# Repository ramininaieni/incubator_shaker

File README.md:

# incubator_shaker
Firmware for an open source incubator shaker to make genetic engineering more accessible

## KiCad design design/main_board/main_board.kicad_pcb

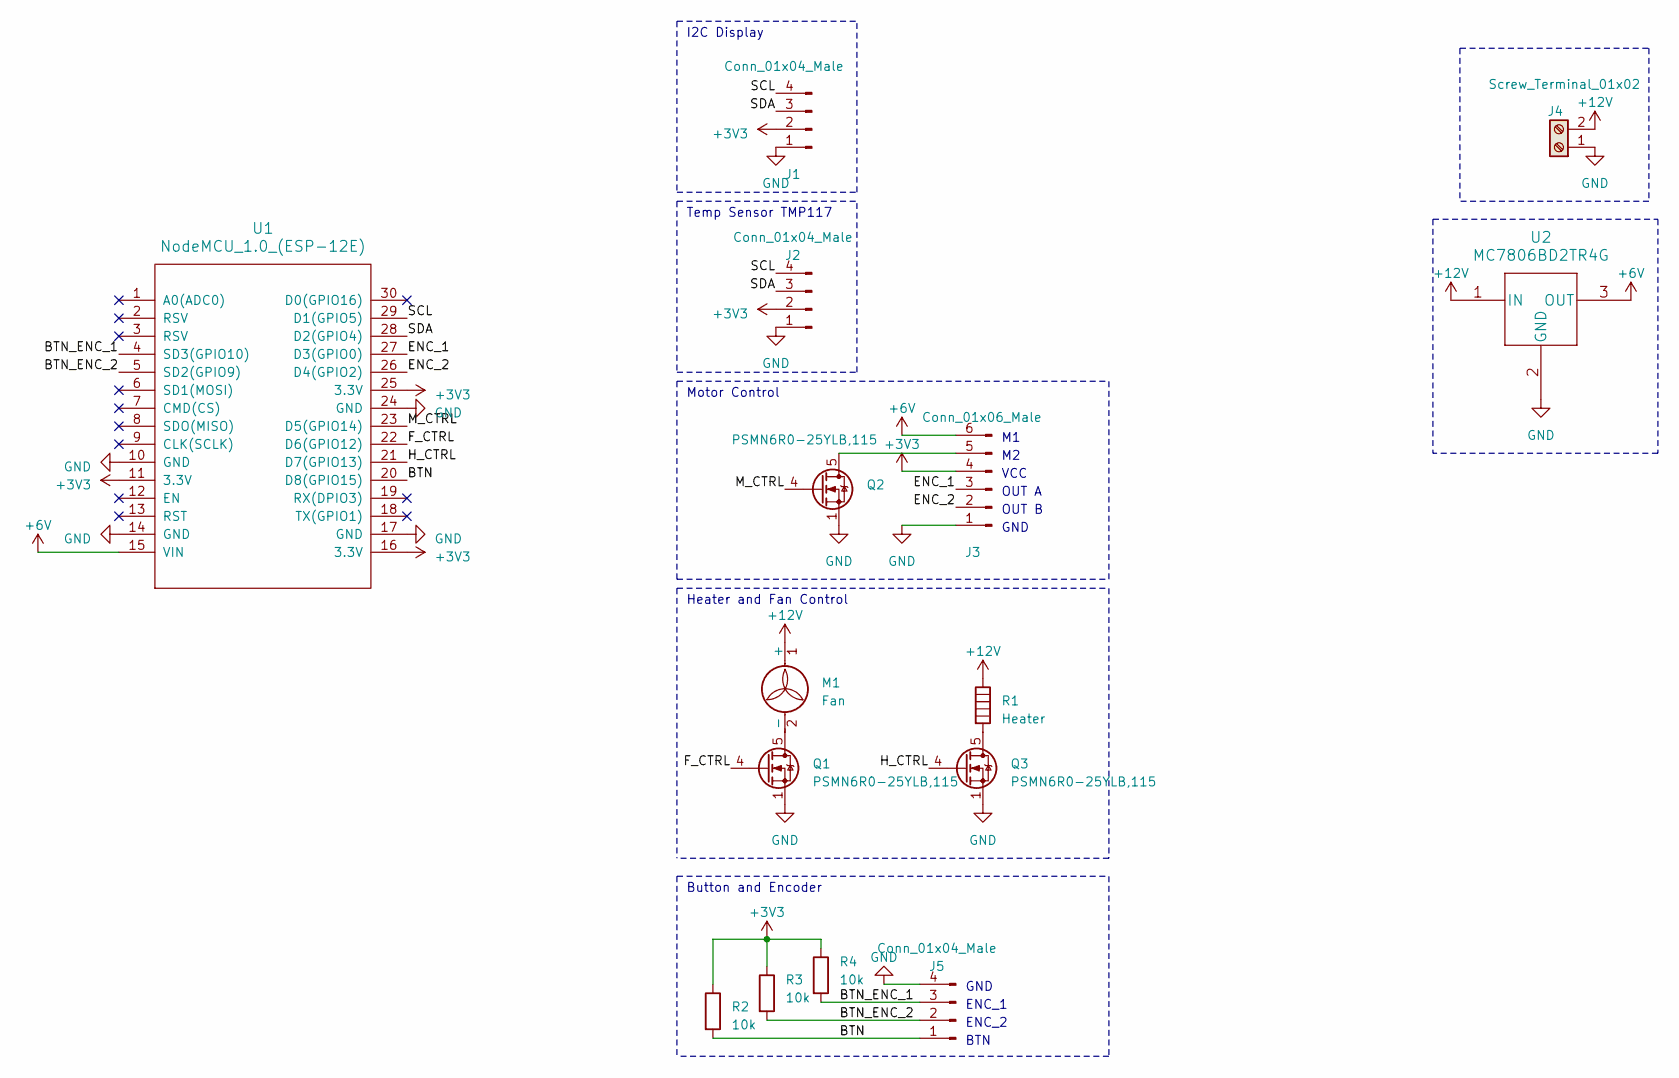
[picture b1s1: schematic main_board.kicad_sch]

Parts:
J1, J2, J5: Conn_01x04_Male; JST_SH_SM04B-SRSS-TB_1x04-1MP_P1.00mm_Horizontal; MFG_PN SM04B-SRSS-TB(LF)(SN)
J3: Conn_01x06_Male; JST_SH_SM06B-SRSS-TB_1x06-1MP_P1.00mm_Horizontal; MFG_PN SM06B-SRSS-TB(LF)(SN)
J4: Screw_Terminal_01x02; TerminalBlock_Phoenix_MKDS-1,5-2-5.08_1x02_P5.08mm_Horizont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; MFG_PN 1715721
M1: Fan; TerminalBlock_Phoenix_MKDS-1,5-2-5.08_1x02_P5.08mm_Horizont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; MFG_PN 1715721
Q1, Q2, Q3: PSMN6R0-25YLB,115; LFPAK56; MFG_PN PSMN6R0-25YLB-115
R1: Heater; TerminalBlock_Phoenix_MKDS-1,5-2-5.08_1x02_P5.08mm_Horizont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; MFG_PN 1715721
R2, R3, R4: 10k; R_0603_1608Metric
U1: NodeMCU_1.0_(ESP-12E); NodeMCU1.0(12-E)
U2: MC7806BD2TR4G; MFG_PN MC7806BD2TR4G

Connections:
+3V3: J1.2, J2.2, J3.4, R2.1, R3.1, R4.1, U1.11 (3.3V), U1.16 (3.3V), U1.25 (3.3V)
+6V: J3.6, U1.15 (VIN), U2.3 (OUT)
+12V: J4.2, M1.1 (+), R1.1, U2.1 (IN)
/BTN: J5.1, R2.2, U1.20 (D8(GPIO15))
/BTN_ENC_1: J5.3, R4.2, U1.4 (SD3(GPIO10))
/BTN_ENC_2: J5.2, R3.2, U1.5 (SD2(GPIO9))
/ENC_1: J3.3, U1.27 (D3(GPIO0))
/ENC_2: J3.2, U1.26 (D4(GPIO2))
/F_CTRL: Q1.4 (G), U1.22 (D6(GPIO12))
/H_CTRL: Q3.4 (G), U1.21 (D7(GPIO13))
/M_CTRL: Q2.4 (G), U1.23 (D5(GPIO14))
/SCL: J1.4, J2.4, U1.29 (D1(GPIO5))
/SDA: J1.3, J2.3, U1.28 (D2(GPIO4))
GND: J1.1, J2.1, J3.1, J4.1, J5.4, Q1.1 (S), Q1.2 (S), Q1.3 (S), Q2.1 (S), Q2.2 (S), Q2.3 (S), Q3.1 (S), Q3.2 (S), Q3.3 (S), U1.10 (GND), U1.14 (GND), U1.17 (GND), U1.24 (GND), U2.2 (GND)
unnamed: J3.5, Q2.5 (D)
unnamed: M1.2 (-), Q1.5 (D)
unnamed: Q3.5 (D), R1.2

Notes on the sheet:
I2C Display
Temp Sensor TMP117
Motor Control
Heater and Fan Control
Button and Encoder
GND
ENC_1
ENC_2
BTN
VCC
OUT A
OUT B

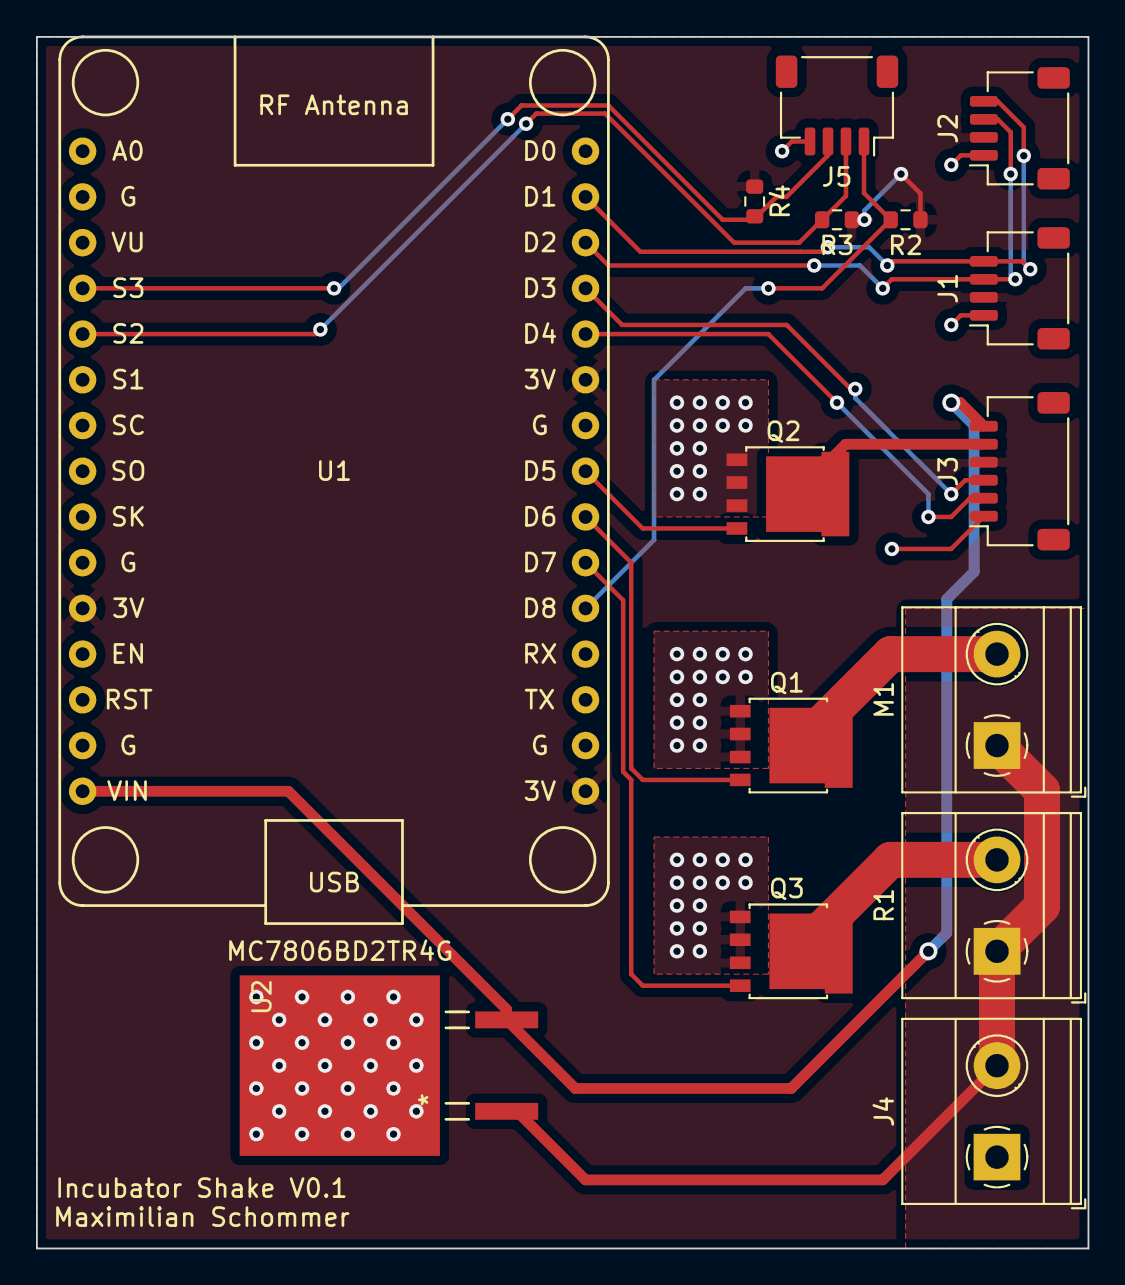
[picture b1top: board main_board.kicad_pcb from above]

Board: 2 copper layers, 58.4 x 67.3 mm, 15 parts (0 on the bottom side), 17 nets.

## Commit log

2021-03-08 Added preliminary motor control code
2021-03-08 Moved files around
2021-03-08 Made RPM detection work. Needs some cleaning up. Next steps are to implement PID control.
2021-03-12 Got PID control working. Still need to make expected RPM is 0 time based on avgnumcycles
2021-04-09 Added temp sensing
2021-04-25 Added initial schematic design and moved firmare to directory
2021-04-26 Finished board layout

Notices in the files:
parts and their libraries:
Copyright 2016 Accelerated Designs. All rights reserved.
